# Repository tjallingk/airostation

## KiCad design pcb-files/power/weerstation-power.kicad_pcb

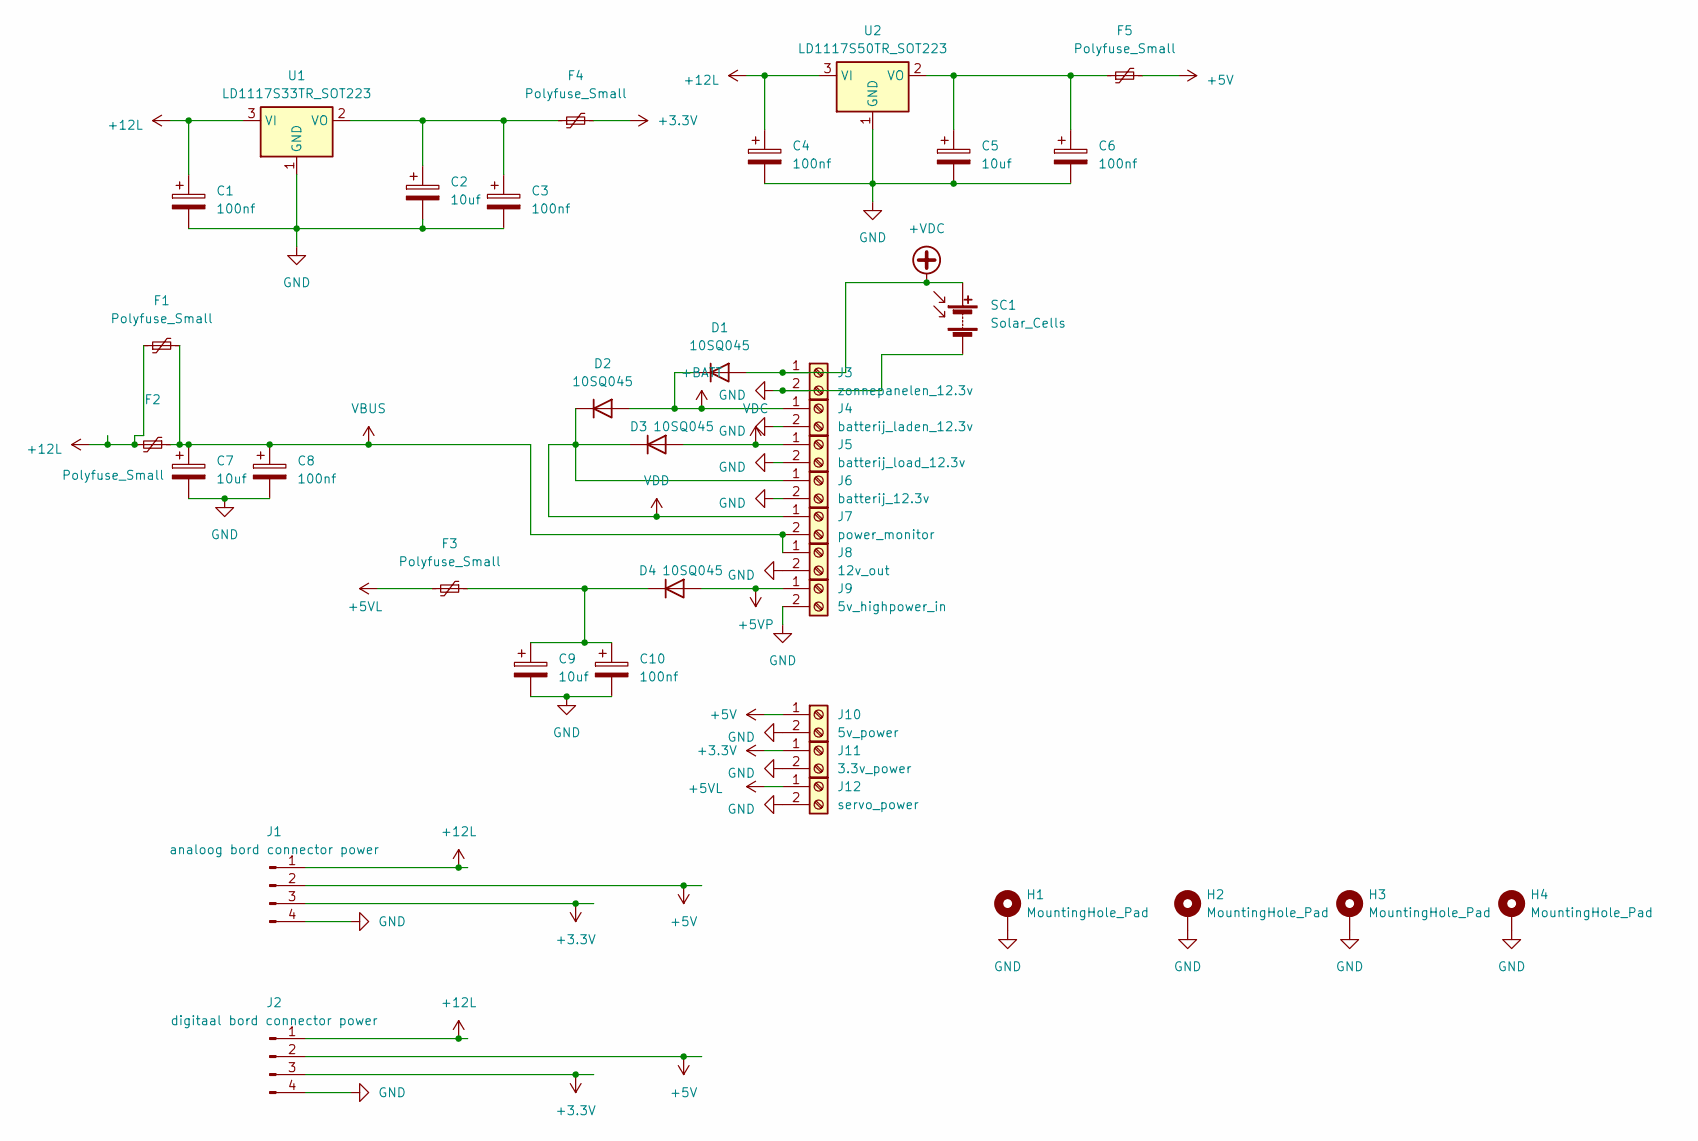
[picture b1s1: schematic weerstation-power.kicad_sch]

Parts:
C1, C3, C4, C6, C8, C10: 100nf; C_1206_3216Metric_Pad1.33x1.80mm_HandSolder
C2, C5, C7, C9: 10uf; C_1206_3216Metric_Pad1.33x1.80mm_HandSolder
D1, D2, D3, D4: 10SQ045; D_P600_R-6_P20.00mm_Horizontal
F1, F2, F3, F4, F5: Polyfuse_Small; Fuse_12060hole_3216Metric_Pad1.42x1.75mm_HandSolder
H1, H2, H3, H4: MountingHole_Pad; MountingHole_4.3mm_M4_Pad
J1: analoog bord connector power; JST_XH_B4B-XH-AM_1x04_P2.50mm_Vertical
J2: digitaal bord connector power; JST_XH_B4B-XH-AM_1x04_P2.50mm_Vertical
J3: zonnepanelen_12.3v; Altech_AK100_1x02_P5.00mm
J4: batterij_laden_12.3v; Altech_AK100_1x02_P5.00mm
J5: batterij_load_12.3v; Altech_AK100_1x02_P5.00mm
J6: batterij_12.3v; Altech_AK100_1x02_P5.00mm
J7: power_monitor; Altech_AK100_1x02_P5.00mm
J8: 12v_out; Altech_AK100_1x02_P5.00mm
J9: 5v_highpower_in; Altech_AK100_1x02_P5.00mm
J10: 5v_power; Altech_AK100_1x02_P5.00mm
J11: 3.3v_power; Altech_AK100_1x02_P5.00mm
J12: servo_power; Altech_AK100_1x02_P5.00mm
SC1: Solar_Cells
U1: LD1117S33TR_SOT223; SOT-223-3_TabPin2
U2: LD1117S50TR_SOT223; SOT-223-3_TabPin2

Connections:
+3.3V: F4.2, J1.3, J2.3, J11.1
+5V: F5.2, J1.2, J2.2, J10.1
+5VL: F3.2, J12.1
+5VP: D4.2 (A), J9.1
+12L: C1.1, C4.1, F1.1, F2.2, J1.1, J2.1, U1.3 (VI), U2.3 (VI)
+BATT: D1.1 (K), D2.2 (A), J4.1
+VDC: D1.2 (A), J3.1, SC1.1 (+)
GND: C1.2, C2.2, C3.2, C4.2, C5.2, C6.2, C7.2, C8.2, C9.2, C10.2, H1.1, H2.1, H3.1, H4.1, J1.4, J2.4, J3.2, J4.2, J5.2, J6.2, J8.2, J9.2, J10.2, J11.2, J12.2, SC1.2 (-), U1.1 (GND), U2.1 (GND)
unnamed: C9.1, C10.1, D4.1 (K), F3.1
unnamed: C2.1, C3.1, F4.1, U1.2 (VO)
unnamed: C5.1, C6.1, F5.1, U2.2 (VO)
VBUS: C7.1, C8.1, F1.2, F2.1, J7.2, J8.1
VDC: D3.2 (A), J5.1
VDD: D2.1 (K), D3.1 (K), J6.1, J7.1

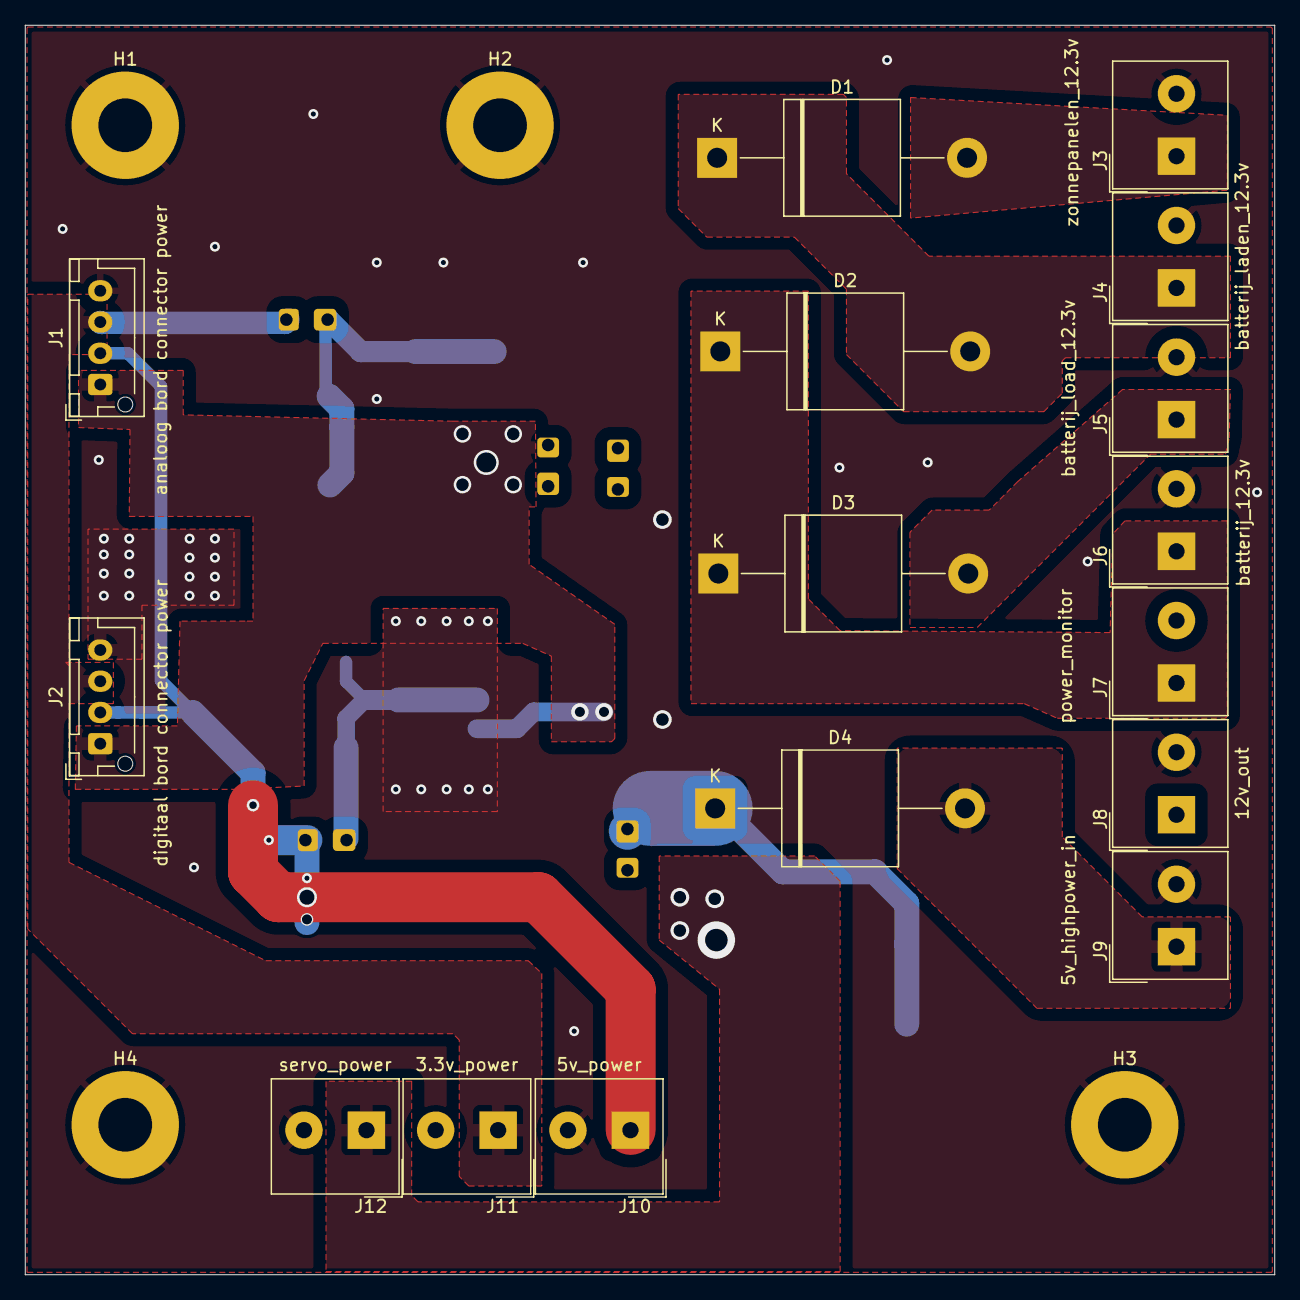
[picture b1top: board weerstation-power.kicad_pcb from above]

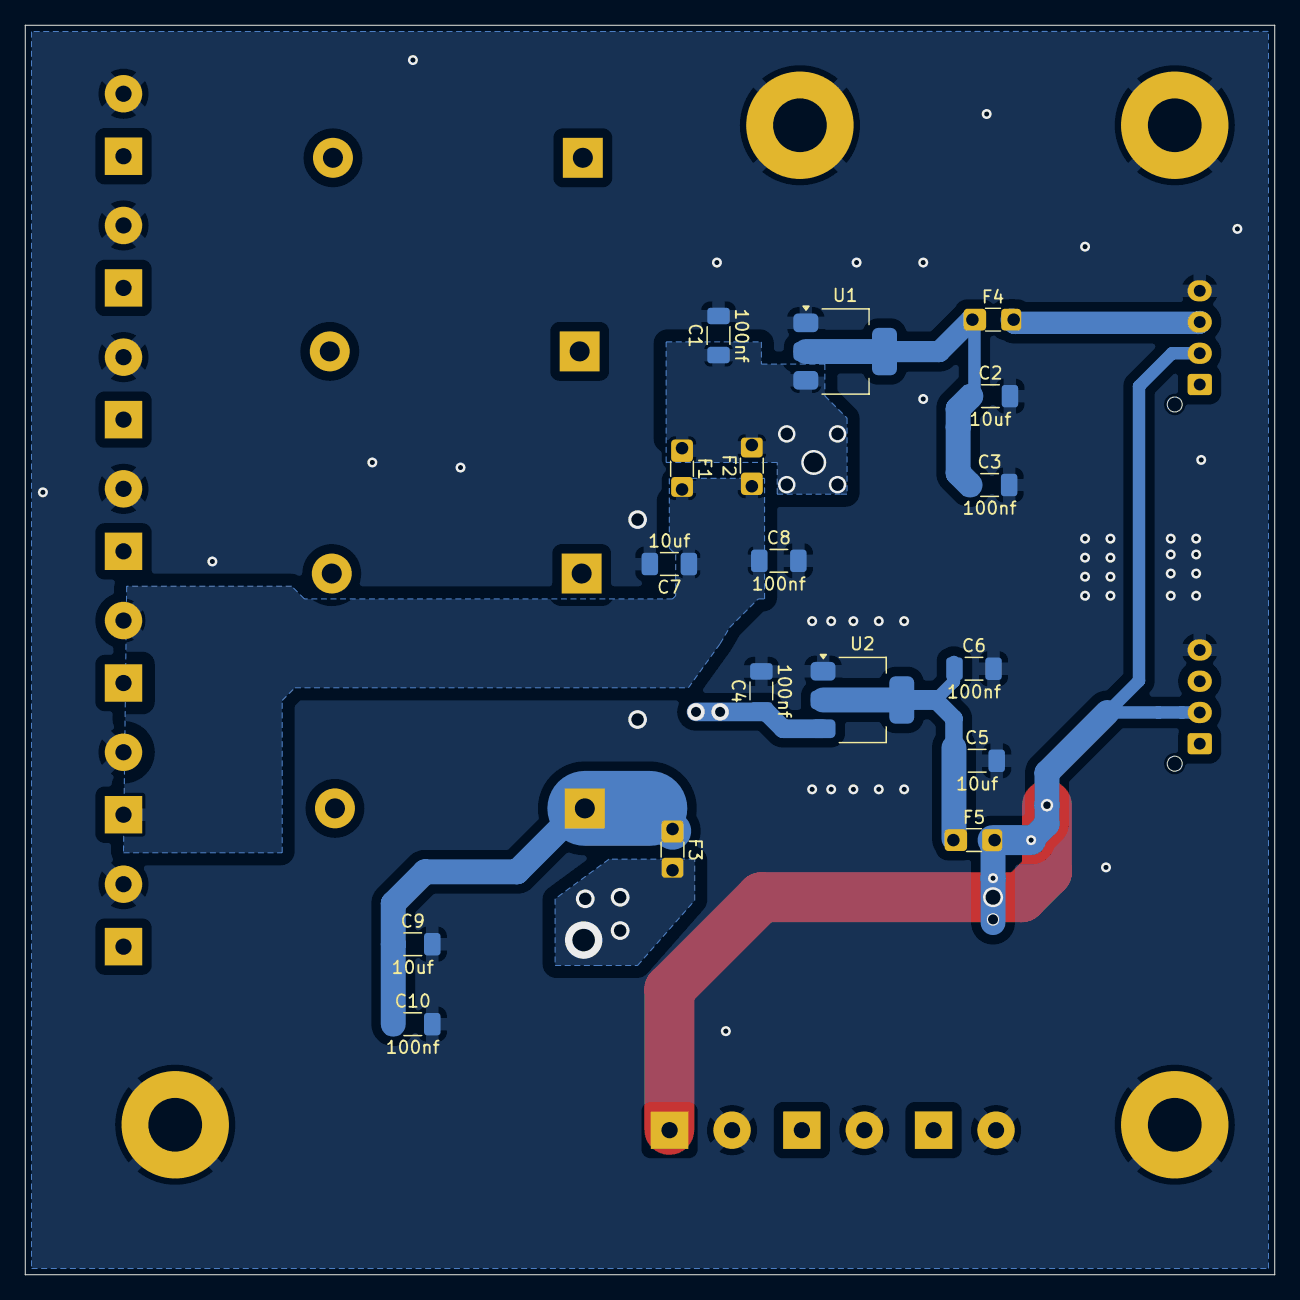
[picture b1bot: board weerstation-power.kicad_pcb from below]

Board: 2 copper layers, 100.0 x 100.0 mm, 37 parts (17 on the bottom side), 14 nets.

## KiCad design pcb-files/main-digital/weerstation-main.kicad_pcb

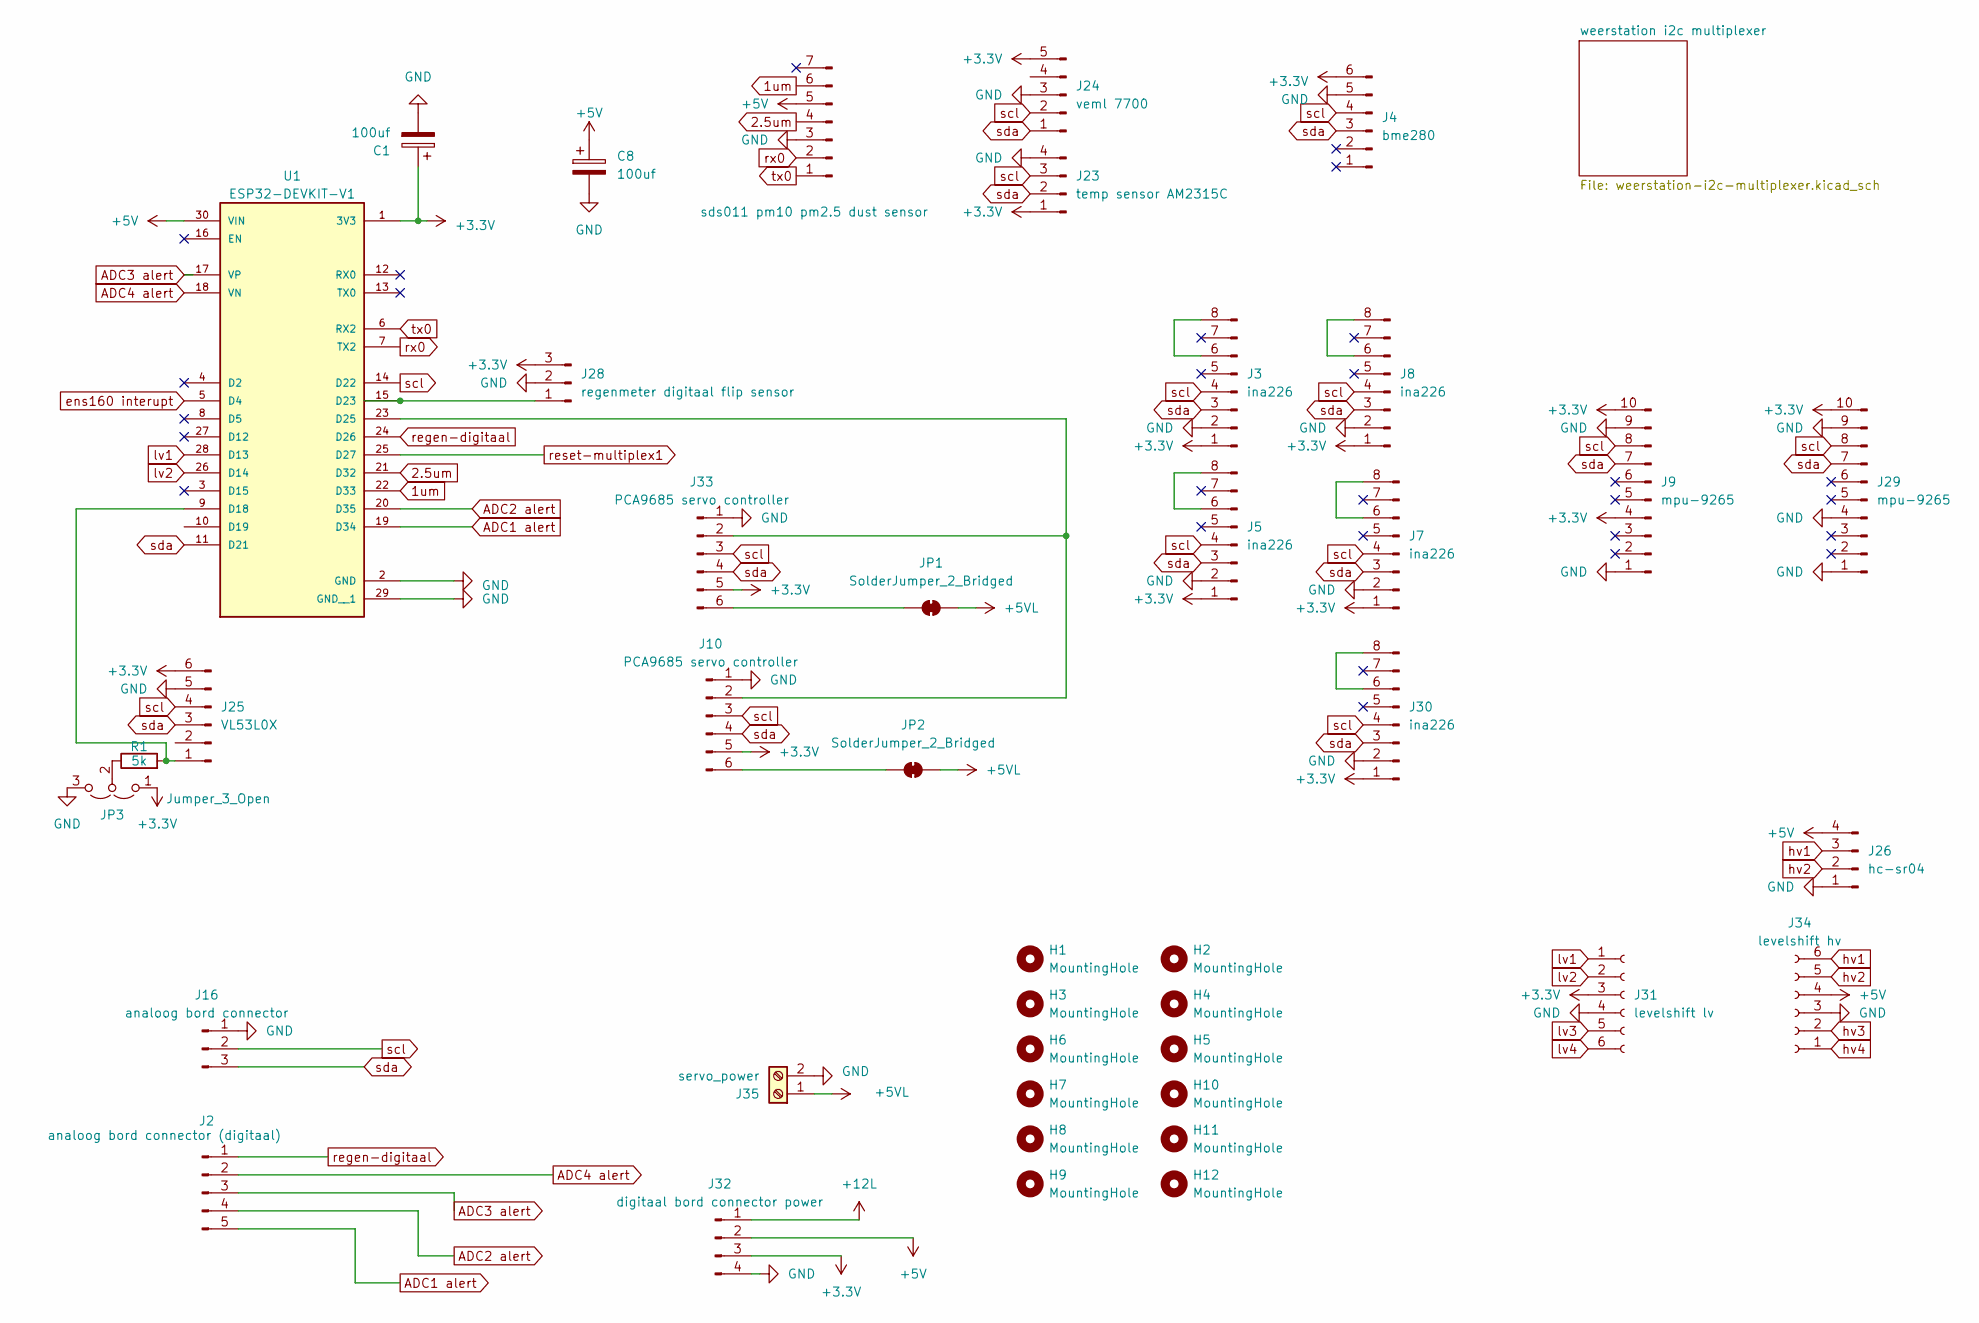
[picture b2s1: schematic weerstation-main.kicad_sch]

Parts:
C1, C8: 100uf; C_1206_3216Metric_Pad1.33x1.80mm_HandSolder
H1, H2, H3, H4, H5, H6, H7, H8, H9, H10, H11, H12: MountingHole; MountingHole_long
J1: sds011 pm10 pm2.5 dust sensor; PinHeader_1x07_P2.54mm_Vertical
J2: analoog bord connector (digitaal); JST_XH_B5B-XH-AM_1x05_P2.50mm_Vertical
J3, J5, J7, J8, J30: ina226; PinHeader_1x08_P2.54mm_Vertical
J4: bme280; PinSocket_1x06_P2.54mm_Vertical
J9, J29: mpu-9265; PinHeader_1x10_P2.54mm_Vertical
J10, J33: PCA9685 servo controller; PinHeader_1x06_P2.54mm_Vertical
J16: analoog bord connector; JST_XH_B3B-XH-AM_1x03_P2.50mm_Vertical
J23: temp sensor AM2315C; PinHeader_1x04_P2.54mm_Vertical
J24: veml 7700; PinHeader_1x05_P2.54mm_Vertical
J25: VL53L0X; PinSocket_1x06_P2.54mm_Vertical
J26: hc-sr04; PinHeader_1x04_P2.54mm_Vertical
J28: regenmeter digitaal flip sensor; PinHeader_1x03_P2.54mm_Vertical
J31: levelshift lv; PinSocket_1x06_P2.54mm_Vertical
J32: digitaal bord connector power; JST_XH_B4B-XH-AM_1x04_P2.50mm_Vertical
J34: levelshift hv; PinSocket_1x06_P2.54mm_Vertical
J35: servo_power; Altech_AK100_1x02_P5.00mm
JP1, JP2: SolderJumper_2_Bridged; SolderJumper-2_P1.3mm_Bridged_RoundedPad1.0x1.5mm
JP3: Jumper_3_Open; SolderJumper-3_P1.3mm_Open_Pad1.0x1.5mm
R1: 5k; R_Axial_DIN0204_L3.6mm_D1.6mm_P5.08mm_Horizontal
U1: ESP32-DEVKIT-V1; MODULE_ESP32_DEVKIT_V1; PARTREV N/A

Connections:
1um: J1.6, U1.22 (D33)
2.5um: J1.4, U1.21 (D32)
+3.3V: C1.1, J3.1, J4.6, J5.1, J7.1, J8.1, J9.4, J9.10, J10.5, J23.1, J24.5, J25.6, J28.3, J29.10, J30.1, J31.3, J32.3, J33.5, JP3.1 (A), U1.1 (3V3); also elsewhere on the board
+5V: C8.1, J1.5, J26.4, J32.2, J34.4, U1.30 (VIN)
+5VL: J35.1, JP1.2 (B), JP2.2 (B)
+12L: J32.1
ADC1 alert: J2.5, U1.19 (D34)
ADC2 alert: J2.4, U1.20 (D35)
ADC3 alert: J2.3, U1.17 (VP)
ADC4 alert: J2.2, U1.18 (VN)
GND: C1.2, C8.2, J1.3, J3.2, J4.5, J5.2, J7.2, J8.2, J9.1, J9.9, J10.1, J16.1, J23.4, J24.3, J25.5, J26.1, J28.2, J29.1, J29.4, J29.9, J30.2, J31.4, J32.4, J33.1, J34.3, J35.2, JP3.3 (B), U1.2 (GND), U1.29 (GND__1); also elsewhere on the board
unnamed: J3.6, J3.8
unnamed: J5.6, J5.8
unnamed: J7.6, J7.8
unnamed: J8.6, J8.8
unnamed: J10.2, J33.2, U1.23 (D25)
unnamed: J10.6, JP2.1 (A)
unnamed: J25.1, R1.2, U1.9 (D18)
unnamed: J28.1, U1.15 (D23)
unnamed: J30.6, J30.8
unnamed: J33.6, JP1.1 (A)
unnamed: JP3.2 (C), R1.1
ens160 interupt: U1.5 (D4); also elsewhere on the board
hv1: J26.3, J34.6
hv2: J26.2, J34.5
hv3: J34.2
hv4: J34.1
lv1: J31.1, U1.28 (D13)
lv2: J31.2, U1.26 (D14)
lv3: J31.5
lv4: J31.6
regen-digitaal: J2.1, U1.24 (D26)
reset-multiplex1: U1.25 (D27)
rx0: J1.2, U1.7 (TX2)
scl: J3.4, J4.4, J5.4, J7.4, J8.4, J9.8, J10.3, J16.2, J23.3, J24.2, J25.4, J29.8, J30.4, J33.3, U1.14 (D22); also elsewhere on the board
sda: J3.3, J4.3, J5.3, J7.3, J8.3, J9.7, J10.4, J16.3, J23.2, J24.1, J25.3, J29.7, J30.3, J33.4, U1.11 (D21); also elsewhere on the board
tx0: J1.1, U1.6 (RX2)

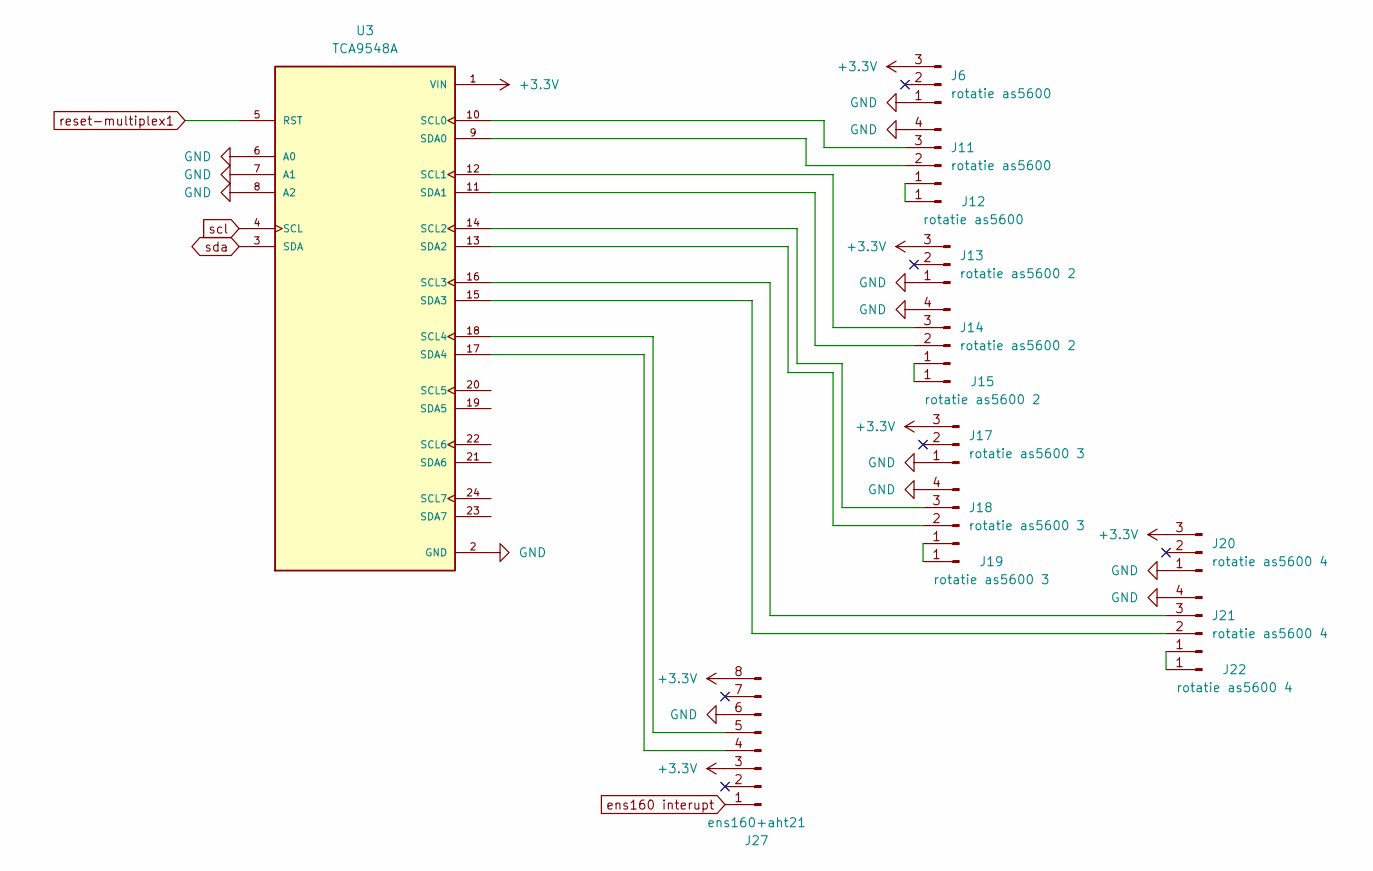
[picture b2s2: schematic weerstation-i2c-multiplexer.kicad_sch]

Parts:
J6: rotatie as5600; PinHeader_1x03_P2.54mm_Vertical
J11: rotatie as5600; PinHeader_1x04_P2.54mm_Vertical
J12: rotatie as5600; PinHeader_1x01_P2.54mm_Vertical
J13: rotatie as5600 2; PinHeader_1x03_P2.54mm_Vertical
J14: rotatie as5600 2; PinHeader_1x04_P2.54mm_Vertical
J15: rotatie as5600 2; PinHeader_1x01_P2.54mm_Vertical
J17: rotatie as5600 3; PinHeader_1x03_P2.54mm_Vertical
J18: rotatie as5600 3; PinHeader_1x04_P2.54mm_Vertical
J19: rotatie as5600 3; PinHeader_1x01_P2.54mm_Vertical
J20: rotatie as5600 4; PinHeader_1x03_P2.54mm_Vertical
J21: rotatie as5600 4; PinHeader_1x04_P2.54mm_Vertical
J22: rotatie as5600 4; PinHeader_1x01_P2.54mm_Vertical
J27: ens160+aht21; PinHeader_1x08_P2.54mm_Vertical
U3: TCA9548A; MODULE_2717; PARTREV Sep 11, 2015

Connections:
+3.3V: J6.3, J13.3, J17.3, J20.3, J27.3, J27.8, U3.1 (VIN); also elsewhere on the board
GND: J6.1, J11.4, J13.1, J14.4, J17.1, J18.4, J20.1, J21.4, J27.6, U3.2 (GND), U3.6 (A0), U3.7 (A1), U3.8 (A2); also elsewhere on the board
unnamed: J11.1, J12.1
unnamed: J11.2, U3.9 (SDA0)
unnamed: J11.3, U3.10 (SCL0)
unnamed: J14.1, J15.1
unnamed: J14.2, U3.11 (SDA1)
unnamed: J14.3, U3.12 (SCL1)
unnamed: J18.1, J19.1
unnamed: J18.2, U3.13 (SDA2)
unnamed: J18.3, U3.14 (SCL2)
unnamed: J21.1, J22.1
unnamed: J21.2, U3.15 (SDA3)
unnamed: J21.3, U3.16 (SCL3)
unnamed: J27.4, U3.17 (SDA4)
unnamed: J27.5, U3.18 (SCL4)
ens160 interupt: J27.1; also elsewhere on the board
scl: U3.4 (SCL); also elsewhere on the board
sda: U3.3 (SDA); also elsewhere on the board

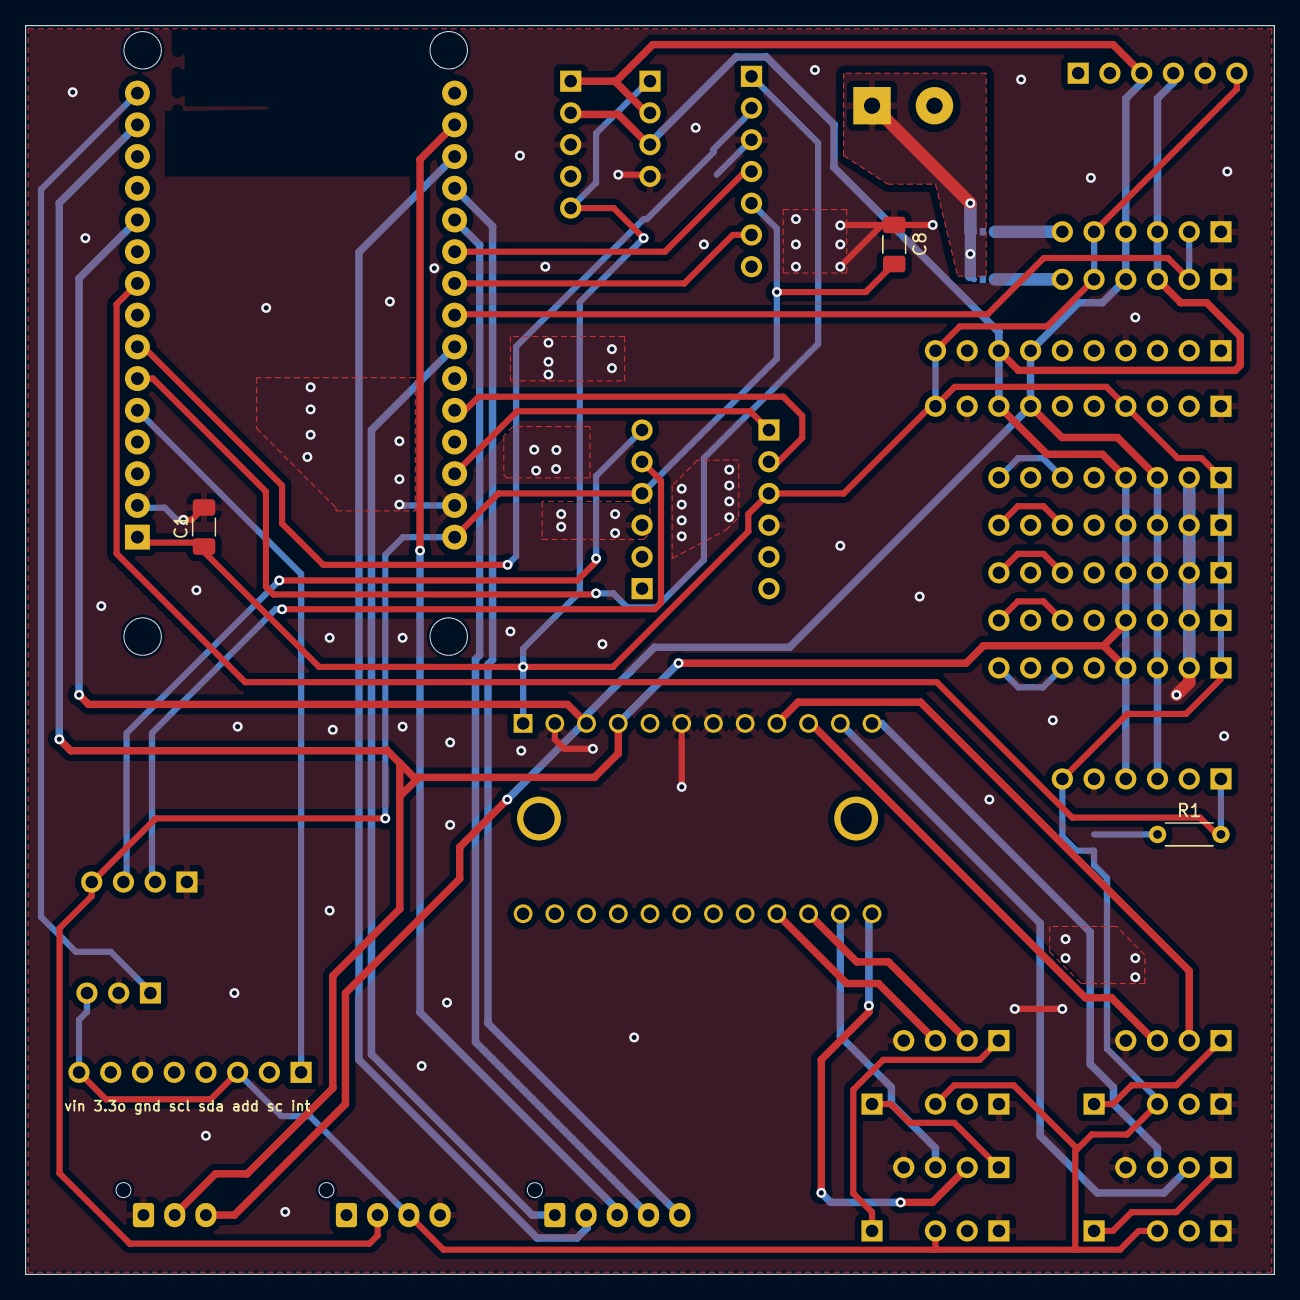
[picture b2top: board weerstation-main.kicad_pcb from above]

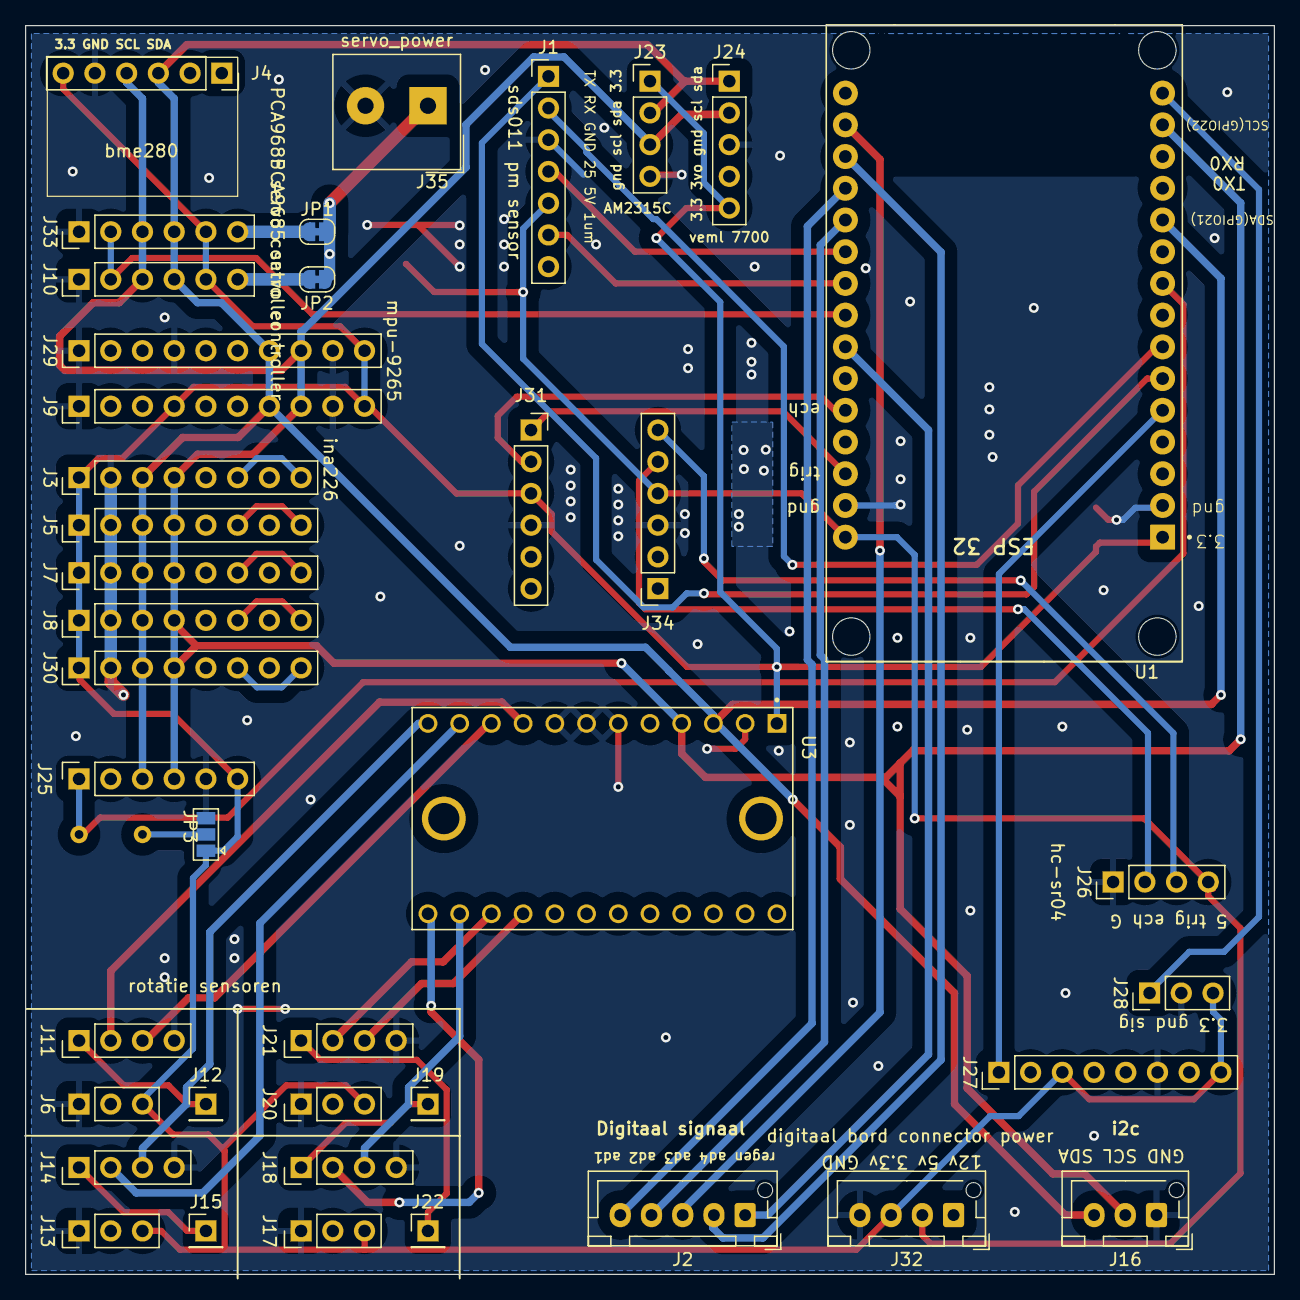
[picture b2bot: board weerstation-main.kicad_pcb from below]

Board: 2 copper layers, 100.0 x 100.0 mm, 55 parts (40 on the bottom side), 43 nets.

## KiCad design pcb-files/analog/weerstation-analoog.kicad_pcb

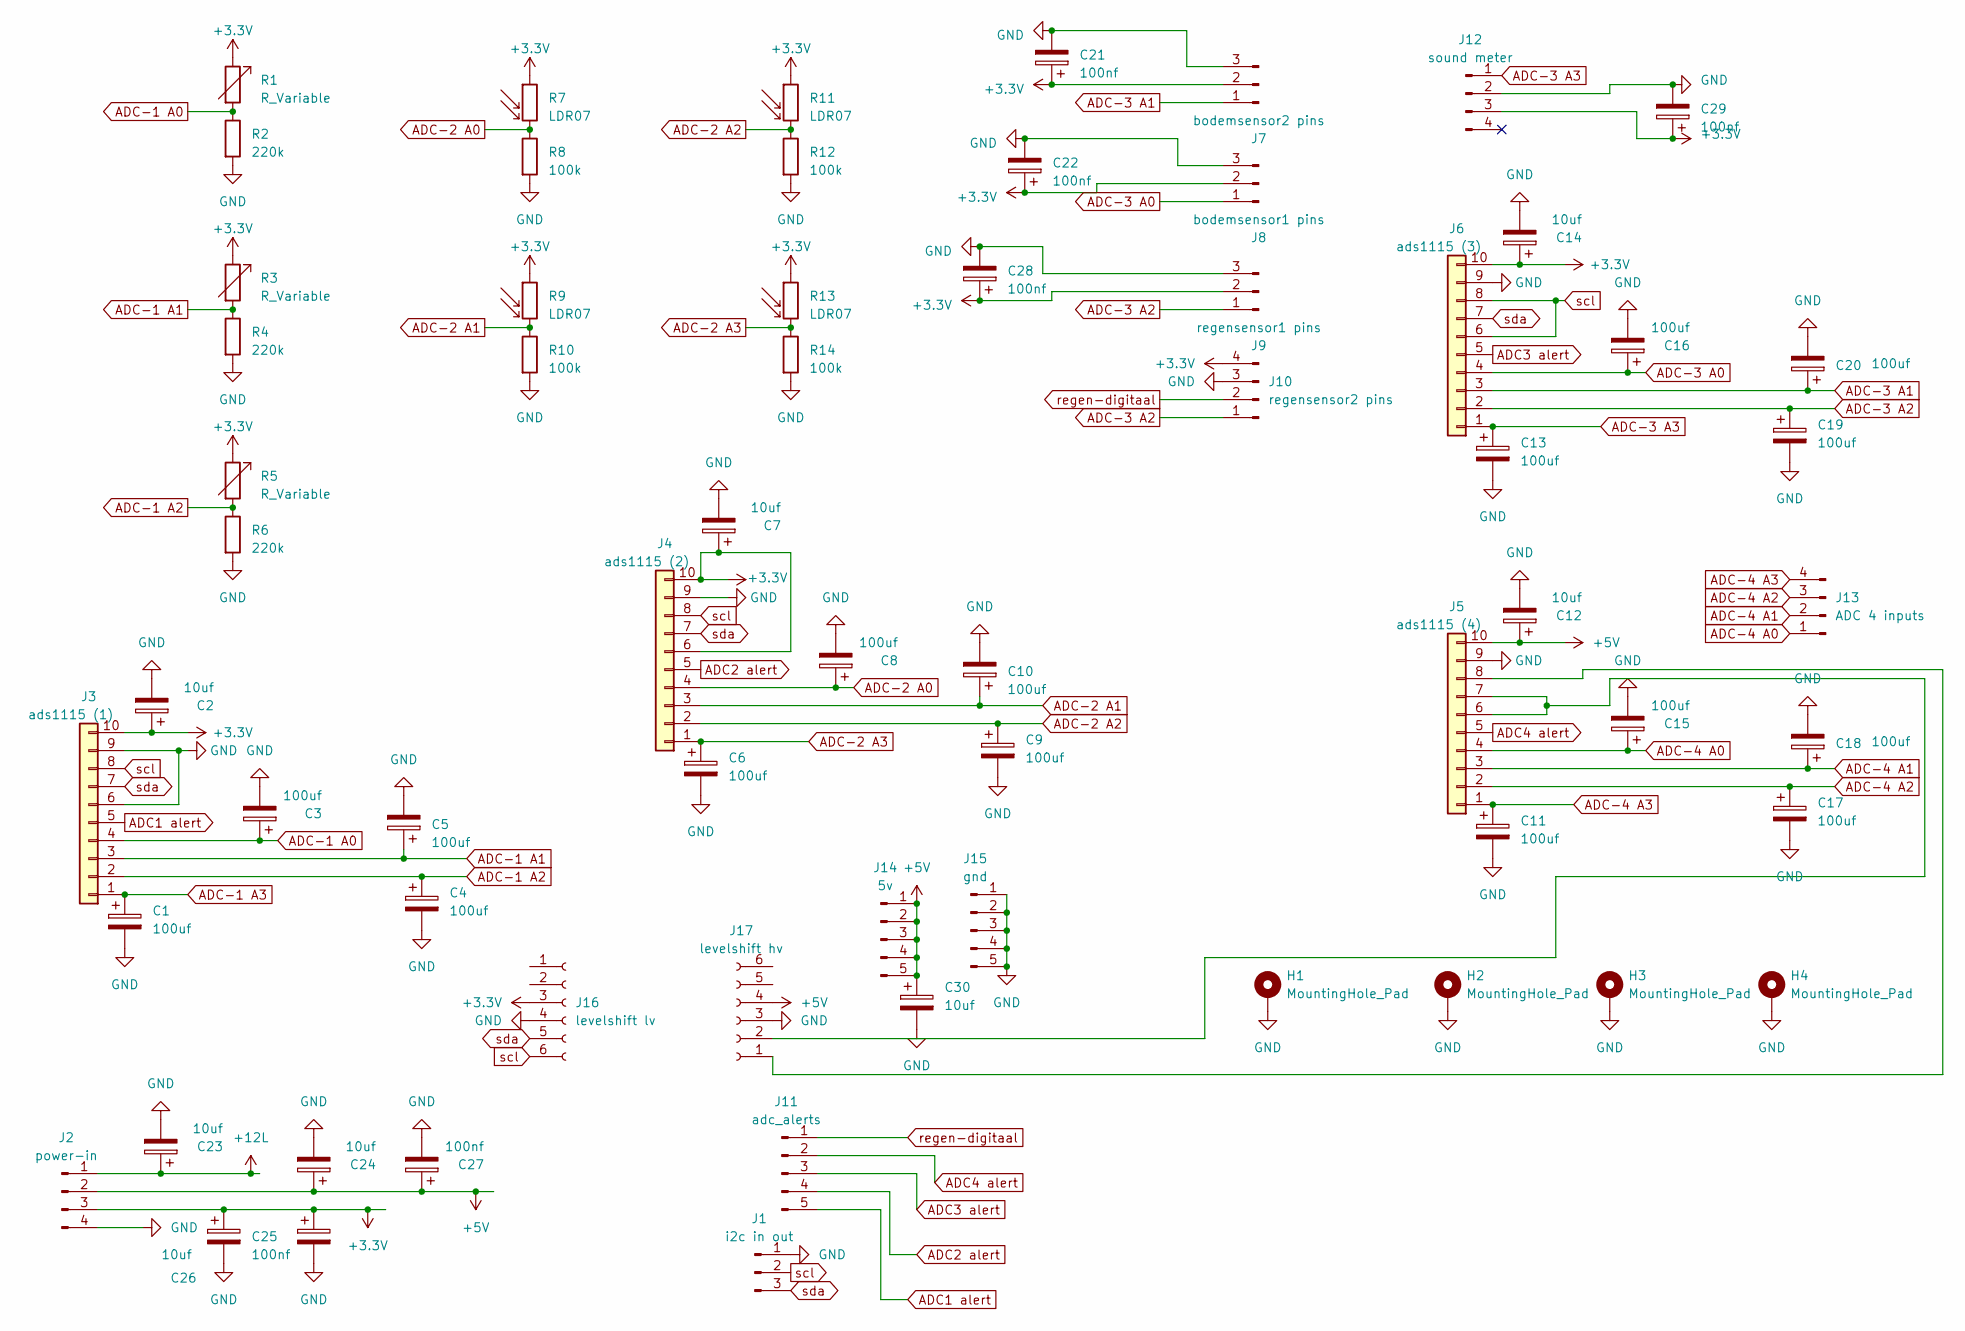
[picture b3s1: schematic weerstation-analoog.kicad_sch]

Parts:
C1, C3, C4, C5, C6, C8, C9, C10, C11, C13, C15, C16, C17, C18, C19, C20: 100uf; C_1206_3216Metric_Pad1.33x1.80mm_HandSolder
C2, C7, C12, C14, C23, C24, C26, C30: 10uf; C_1206_3216Metric_Pad1.33x1.80mm_HandSolder
C21, C22, C25, C27, C28, C29: 100nf; C_1206_3216Metric_Pad1.33x1.80mm_HandSolder
H1, H2, H3, H4: MountingHole_Pad; MountingHole_2.7mm_M2.5_Pad
J1: i2c in out; JST_XH_B3B-XH-AM_1x03_P2.50mm_Vertical
J2: power-in; JST_XH_B4B-XH-AM_1x04_P2.50mm_Vertical
J3: ads1115 (1); PinSocket_1x10_P2.54mm_Vertical
J4: ads1115 (2); PinSocket_1x10_P2.54mm_Vertical
J5: ads1115 (4); PinSocket_1x10_P2.54mm_Vertical
J6: ads1115 (3); PinSocket_1x10_P2.54mm_Vertical
J7: bodemsensor2 pins; PinHeader_1x03_P2.54mm_Vertical
J8: bodemsensor1 pins; PinHeader_1x03_P2.54mm_Vertical
J9: regensensor1 pins; PinHeader_1x03_P2.54mm_Vertical
J10: regensensor2 pins; PinHeader_1x04_P2.54mm_Vertical
J11: adc_alerts; JST_XH_B5B-XH-AM_1x05_P2.50mm_Vertical
J12: sound meter; PinHeader_1x04_P2.54mm_Vertical
J13: ADC 4 inputs; PinHeader_1x04_P2.54mm_Vertical
J14: 5v; PinHeader_1x05_P2.54mm_Vertical
J15: gnd; PinHeader_1x05_P2.54mm_Vertical
J16: levelshift lv; PinSocket_1x06_P2.54mm_Vertical
J17: levelshift hv; PinSocket_1x06_P2.54mm_Vertical
R1, R3, R5: R_Variable; JST_XH_B2B-XH-AM_1x02_P2.50mm_Vertical
R2, R4, R6: 220k; R_Axial_DIN0204_L3.6mm_D1.6mm_P7.62mm_Horizontal
R7, R9, R11, R13: LDR07; PinHeader_1x02_P2.54mm_Vertical
R8, R10, R12, R14: 100k; R_Axial_DIN0204_L3.6mm_D1.6mm_P7.62mm_Horizontal

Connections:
+3.3V: C2.1, C7.1, C14.1, C21.1, C22.1, C25.1, C26.1, C28.1, C29.1, J2.3, J3.10, J4.6, J4.10, J6.10, J7.2, J8.2, J9.2, J10.4, J12.3, J16.3, R1.1, R3.1, R5.1, R7.1, R9.1, R11.1, R13.1
+5V: C12.1, C24.1, C27.1, C30.1, J2.2, J5.10, J14.1, J14.2, J14.3, J14.4, J14.5, J17.4
+12L: C23.1, J2.1
ADC1 alert: J3.5, J11.5
ADC2 alert: J4.5, J11.4
ADC3 alert: J6.5, J11.3
ADC4 alert: J5.5, J11.2
ADC-1 A0: C3.1, J3.4, R1.2, R2.1
ADC-1 A1: C5.1, J3.3, R3.2, R4.1
ADC-1 A2: C4.1, J3.2, R5.2, R6.1
ADC-1 A3: C1.1, J3.1
ADC-2 A0: C8.1, J4.4, R7.2, R8.1
ADC-2 A1: C10.1, J4.3, R9.2, R10.1
ADC-2 A2: C9.1, J4.2, R11.2, R12.1
ADC-2 A3: C6.1, J4.1, R13.2, R14.1
ADC-3 A0: C16.1, J6.4, J8.1
ADC-3 A1: C20.1, J6.3, J7.1
ADC-3 A2: C19.1, J6.2, J9.1, J10.1
ADC-3 A3: C13.1, J6.1, J12.1
ADC-4 A0: C15.1, J5.4, J13.1
ADC-4 A1: C18.1, J5.3, J13.2
ADC-4 A2: C17.1, J5.2, J13.3
ADC-4 A3: C11.1, J5.1, J13.4
GND: C1.2, C2.2, C3.2, C4.2, C5.2, C6.2, C7.2, C8.2, C9.2, C10.2, C11.2, C12.2, C13.2, C14.2, C15.2, C16.2, C17.2, C18.2, C19.2, C20.2, C21.2, C22.2, C23.2, C24.2, C25.2, C26.2, C27.2, C28.2, C29.2, C30.2, H1.1, H2.1, H3.1, H4.1, J1.1, J2.4, J3.6, J3.9, J4.9, J5.9, J6.9, J7.3, J8.3, J9.3, J10.3, J12.2, J15.1, J15.2, J15.3, J15.4, J15.5, J16.4, J17.3, R2.2, R4.2, R6.2, R8.2, R10.2, R12.2, R14.2
unnamed: J5.8, J17.1
unnamed: J5.6, J5.7, J17.2
regen-digitaal: J10.2, J11.1
scl: J1.2, J3.8, J4.8, J6.6, J6.8, J16.6
sda: J1.3, J3.7, J4.7, J6.7, J16.5
